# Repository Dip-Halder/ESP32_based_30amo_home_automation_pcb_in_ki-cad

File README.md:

# ESP32_based_30amp_home_automation_pcb_in_ki-cad

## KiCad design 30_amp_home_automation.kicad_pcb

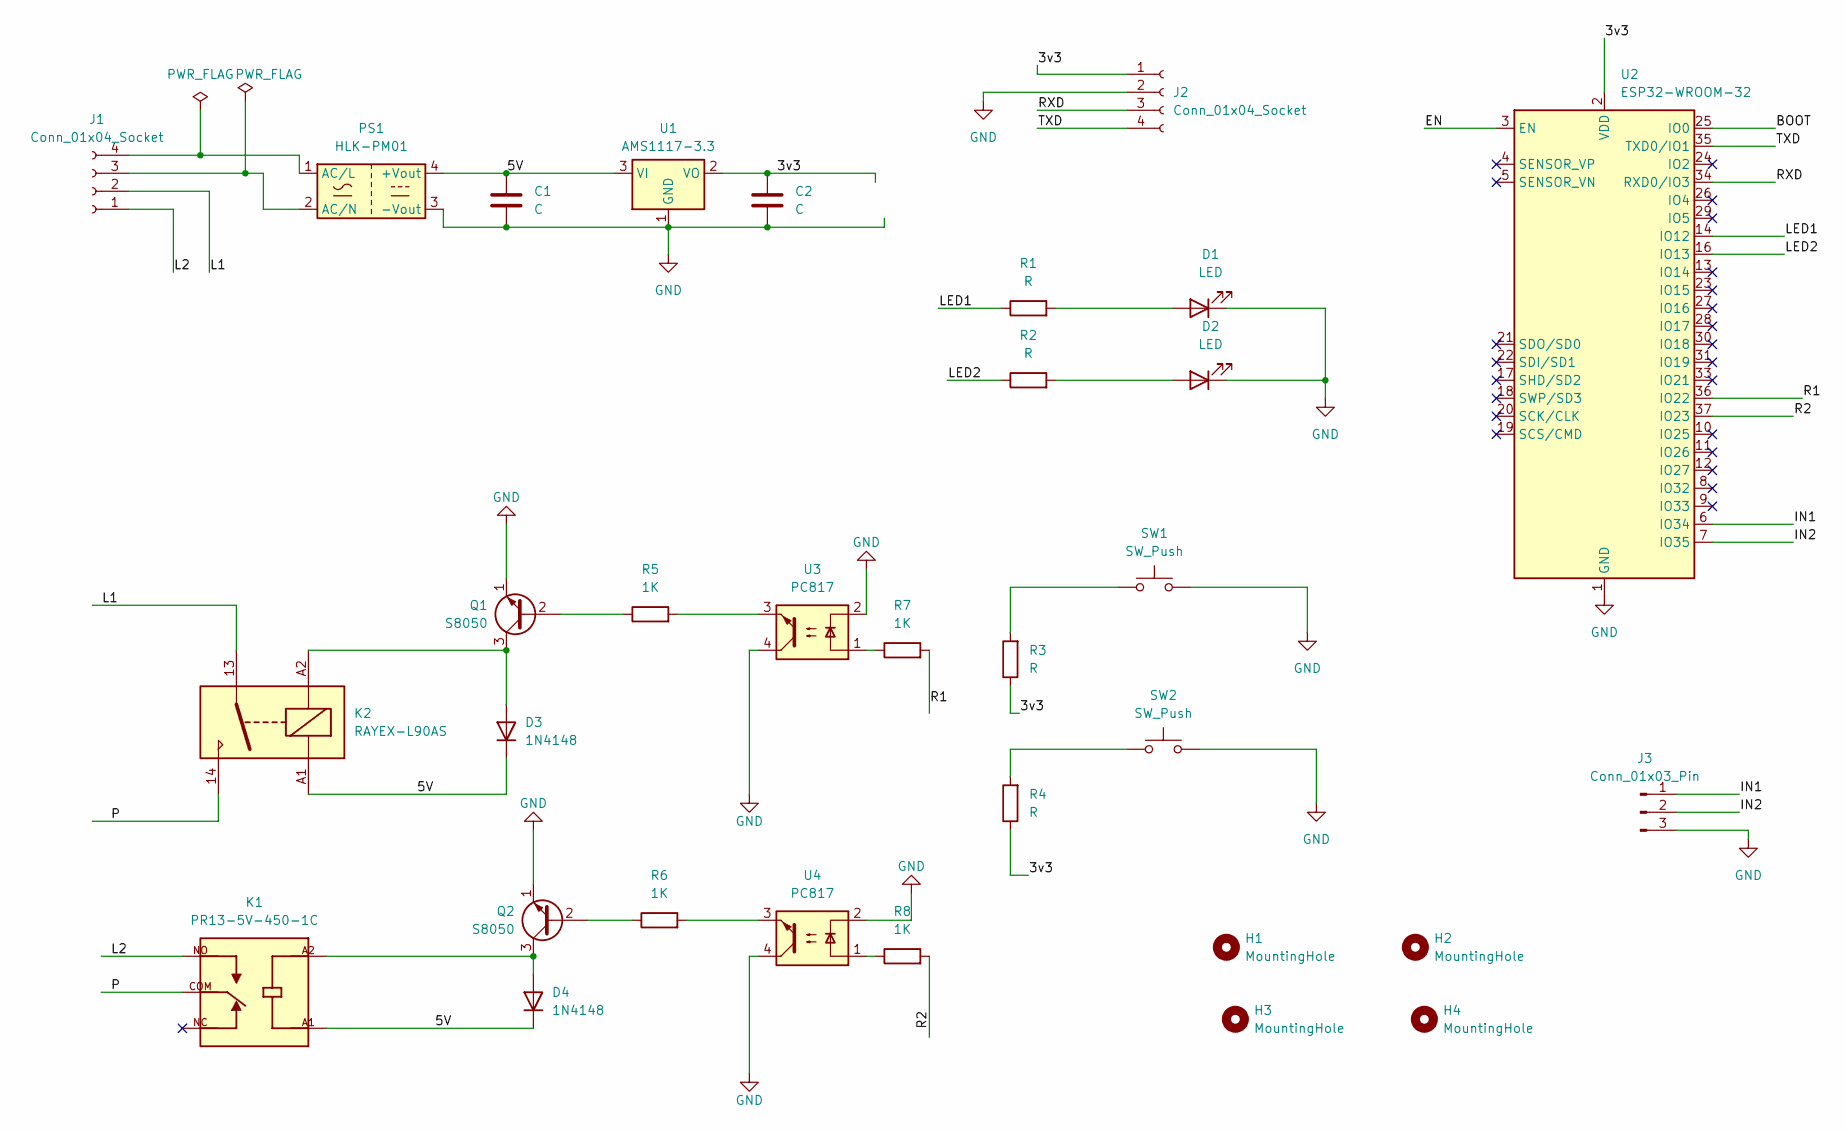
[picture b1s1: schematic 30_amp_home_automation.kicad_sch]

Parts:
C1, C2: C; C_0805_2012Metric
D1, D2: LED; LED_0805_2012Metric
D3, D4: 1N4148; D_DO-35_SOD27_P7.62mm_Horizontal
H1, H2, H3, H4: MountingHole; MountingHole_2.7mm_Pad_Via
J1: Conn_01x04_Socket; TerminalBlock_bornier-4_P5.08mm
J2: Conn_01x04_Socket; PinHeader_1x04_P2.54mm_Vertical
J3: Conn_01x03_Pin; TerminalBlock_bornier-4_P5.08mm
K1: PR13-5V-450-1C; RELAY_PR13-5V-450-1C; PARTREV 1.0
K2: RAYEX-L90AS; Relay_SPST_RAYEX-L90AS
PS1: HLK-PM01; Converter_ACDC_Hi-Link_HLK-PMxx
Q1, Q2: S8050; TO-92_Inline
R1, R2, R3, R4: R; R_0805_2012Metric
R5, R6, R7, R8: 1K; R_0805_2012Metric
SW1, SW2: SW_Push; SW_PUSH_6mm
U1: AMS1117-3.3; SOT-223-3_TabPin2
U2: ESP32-WROOM-32
U3, U4: PC817; DIP-4_W7.62mm

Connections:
/3v3: C2.1, J2.1, R3.1, R4.1, U1.2 (VO), U2.2 (VDD)
/5V: C1.1, D3.1 (K), D4.1 (K), K1.A1, K2.A1, PS1.4 (+Vout), U1.3 (VI)
/BOOT: U2.25 (IO0)
/EN: U2.3 (EN)
/IN1: J3.1, U2.6 (IO34)
/IN2: J3.2, U2.7 (IO35)
/L1: J1.2, K2.13
/L2: J1.1, K1.NO
/LED1: R1.1, U2.14 (IO12)
/LED2: R2.1, U2.16 (IO13)
/P: K1.COM, K2.14
/R1: R7.2, U2.36 (IO22)
/R2: R8.2, U2.37 (IO23)
/RXD: J2.3, U2.34 (RXD0/IO3)
/TXD: J2.4, U2.35 (TXD0/IO1)
GND: C1.2, C2.2, D1.1 (K), D2.1 (K), J2.2, J3.3, PS1.3 (-Vout), Q1.1 (E), Q2.1 (E), SW1.2, SW2.2, U1.1 (GND), U2.1 (GND), U2.15 (GND), U2.38 (GND), U2.39 (GND), U3.2, U3.4, U4.2, U4.4
unnamed: D1.2 (A), R1.2
unnamed: D2.2 (A), R2.2
unnamed: D3.2 (A), K2.A2, Q1.3 (C)
unnamed: D4.2 (A), K1.A2, Q2.3 (C)
unnamed: J1.3, PS1.2 (AC/N)
unnamed: J1.4, PS1.1 (AC/L)
unnamed: Q1.2 (B), R5.1
unnamed: Q2.2 (B), R6.1
unnamed: R3.2, SW1.1
unnamed: R4.2, SW2.1
unnamed: R5.2, U3.3
unnamed: R6.2, U4.3
unnamed: R7.1, U3.1
unnamed: R8.1, U4.1

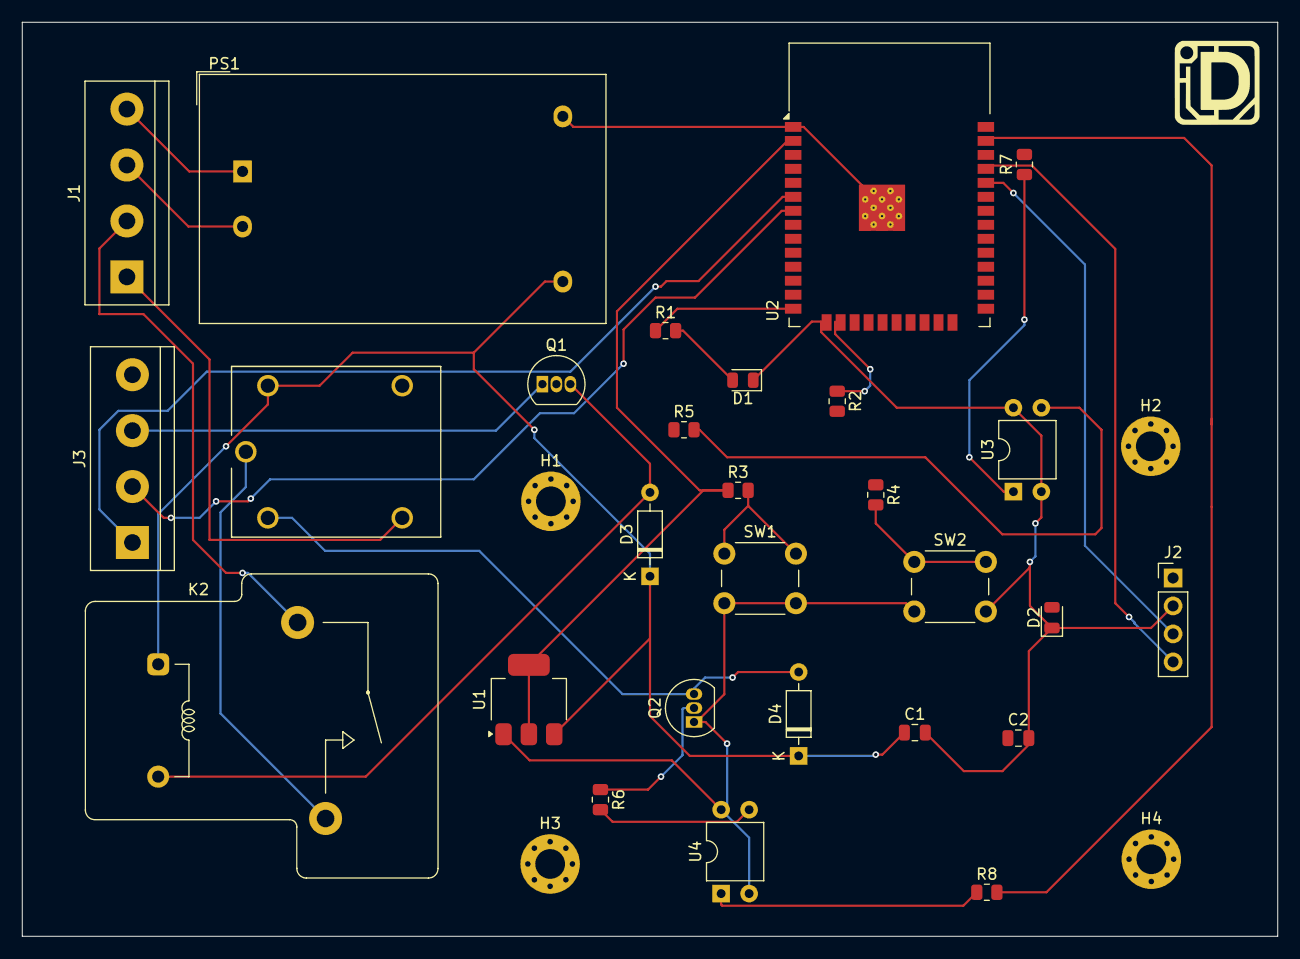
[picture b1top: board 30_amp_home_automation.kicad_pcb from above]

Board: 2 copper layers, 114.0 x 83.0 mm, 32 parts (0 on the bottom side), 28 nets.
